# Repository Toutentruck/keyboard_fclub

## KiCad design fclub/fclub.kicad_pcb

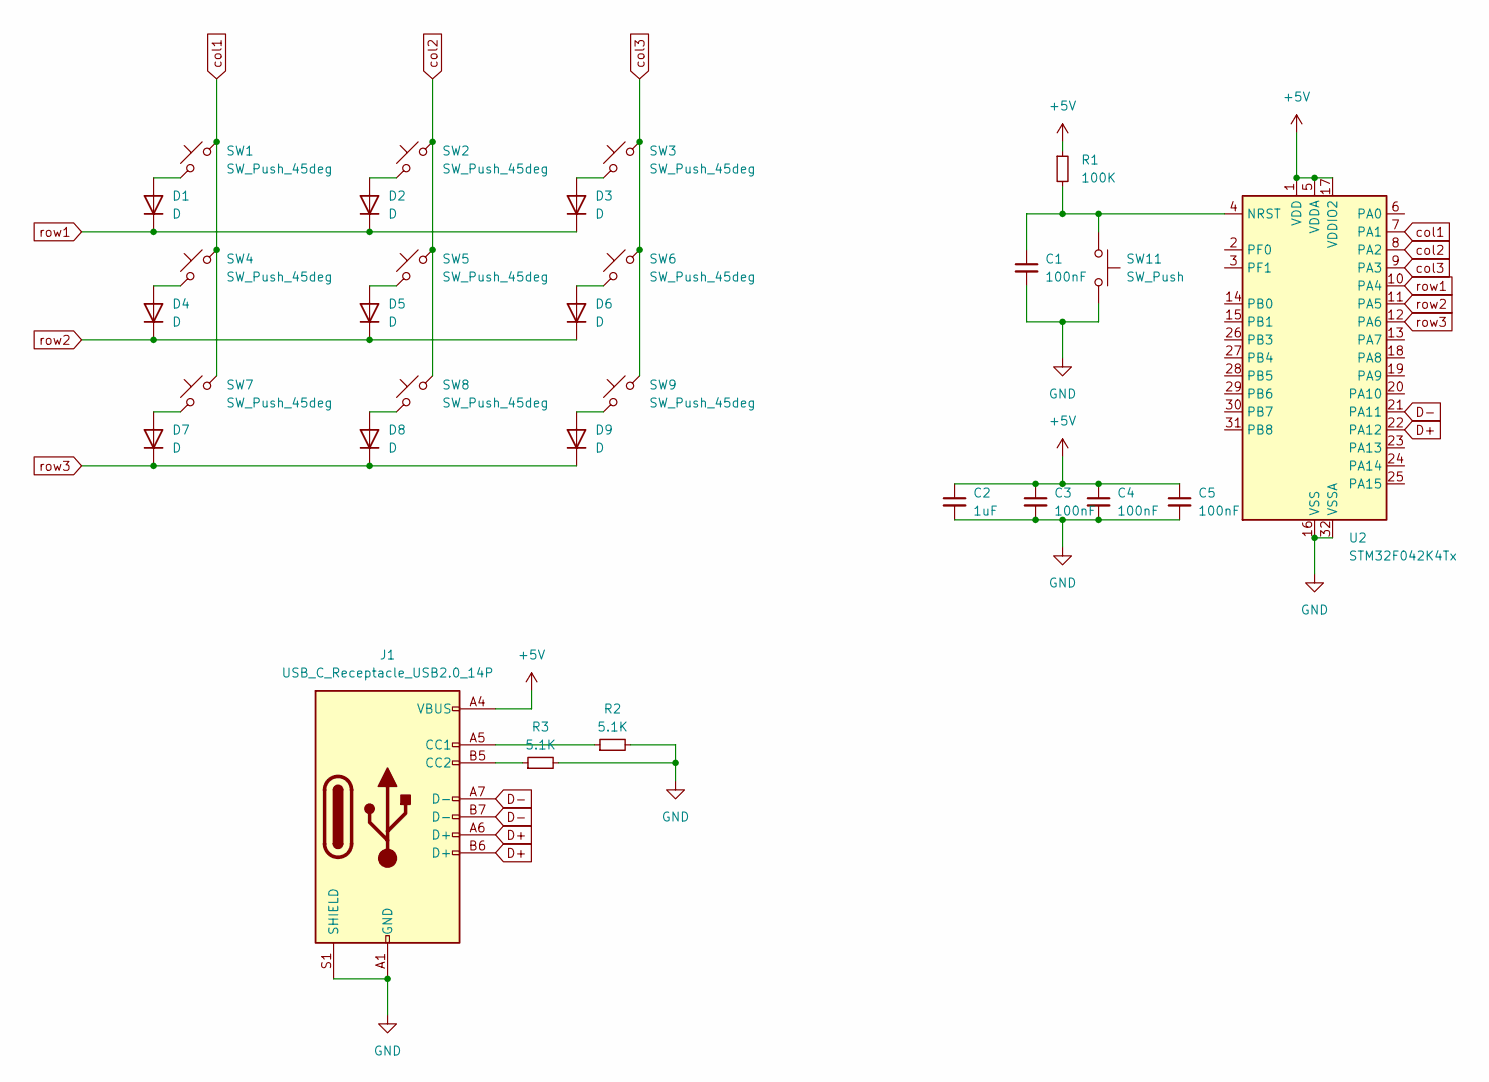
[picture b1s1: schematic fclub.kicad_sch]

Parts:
C1, C3, C4, C5: 100nF; C_0201_0603Metric_Pad0.64x0.40mm_HandSolder
C2: 1uF; C_0201_0603Metric_Pad0.64x0.40mm_HandSolder
D1, D2, D3, D4, D5, D6, D7, D8, D9: D; D_SOD-323_HandSoldering
J1: USB_C_Receptacle_USB2.0_14P; USB_C_Receptacle_GCT_USB4105-xx-A_16P_TopMnt_Horizontal
R1: 100K; R_0201_0603Metric_Pad0.64x0.40mm_HandSolder
R2, R3: 5.1K; R_0201_0603Metric_Pad0.64x0.40mm_HandSolder
SW1, SW2, SW3, SW4, SW5, SW6, SW7, SW8, SW9: SW_Push_45deg; SW_MX_1u
SW11: SW_Push; SKQG-1155865
U2: STM32F042K4Tx; LQFP-32_7x7mm_P0.8mm

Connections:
+5V: C2.1, C3.1, C4.1, C5.1, J1.A4 (VBUS), J1.A9 (VBUS), J1.B4 (VBUS), J1.B9 (VBUS), R1.1, U2.1 (VDD), U2.5 (VDDA), U2.17 (VDDIO2)
D+: J1.A6 (D+), J1.B6 (D+), U2.22 (PA12)
D-: J1.A7 (D-), J1.B7 (D-), U2.21 (PA11)
GND: C1.2, C2.2, C3.2, C4.2, C5.2, J1.A1 (GND), J1.A12 (GND), J1.B1 (GND), J1.B12 (GND), J1.S1 (SHIELD), R2.2, R3.2, SW11.2, U2.16 (VSS), U2.32 (VSSA)
unnamed: D1.2 (A), SW1.1
unnamed: D2.2 (A), SW2.1
unnamed: D3.2 (A), SW3.1
unnamed: D4.2 (A), SW4.1
unnamed: D5.2 (A), SW5.1
unnamed: D6.2 (A), SW6.1
unnamed: D7.2 (A), SW7.1
unnamed: D8.2 (A), SW8.1
unnamed: D9.2 (A), SW9.1
unnamed: J1.A5 (CC1), R2.1
unnamed: J1.B5 (CC2), R3.1
unnamed: C1.1, R1.2, SW11.1, U2.4 (NRST)
col1: SW1.2, SW4.2, SW7.2, U2.7 (PA1)
col2: SW2.2, SW5.2, SW8.2, U2.8 (PA2)
col3: SW3.2, SW6.2, SW9.2, U2.9 (PA3)
row1: D1.1 (K), D2.1 (K), D3.1 (K), U2.10 (PA4)
row2: D4.1 (K), D5.1 (K), D6.1 (K), U2.11 (PA5)
row3: D7.1 (K), D8.1 (K), D9.1 (K), U2.12 (PA6)

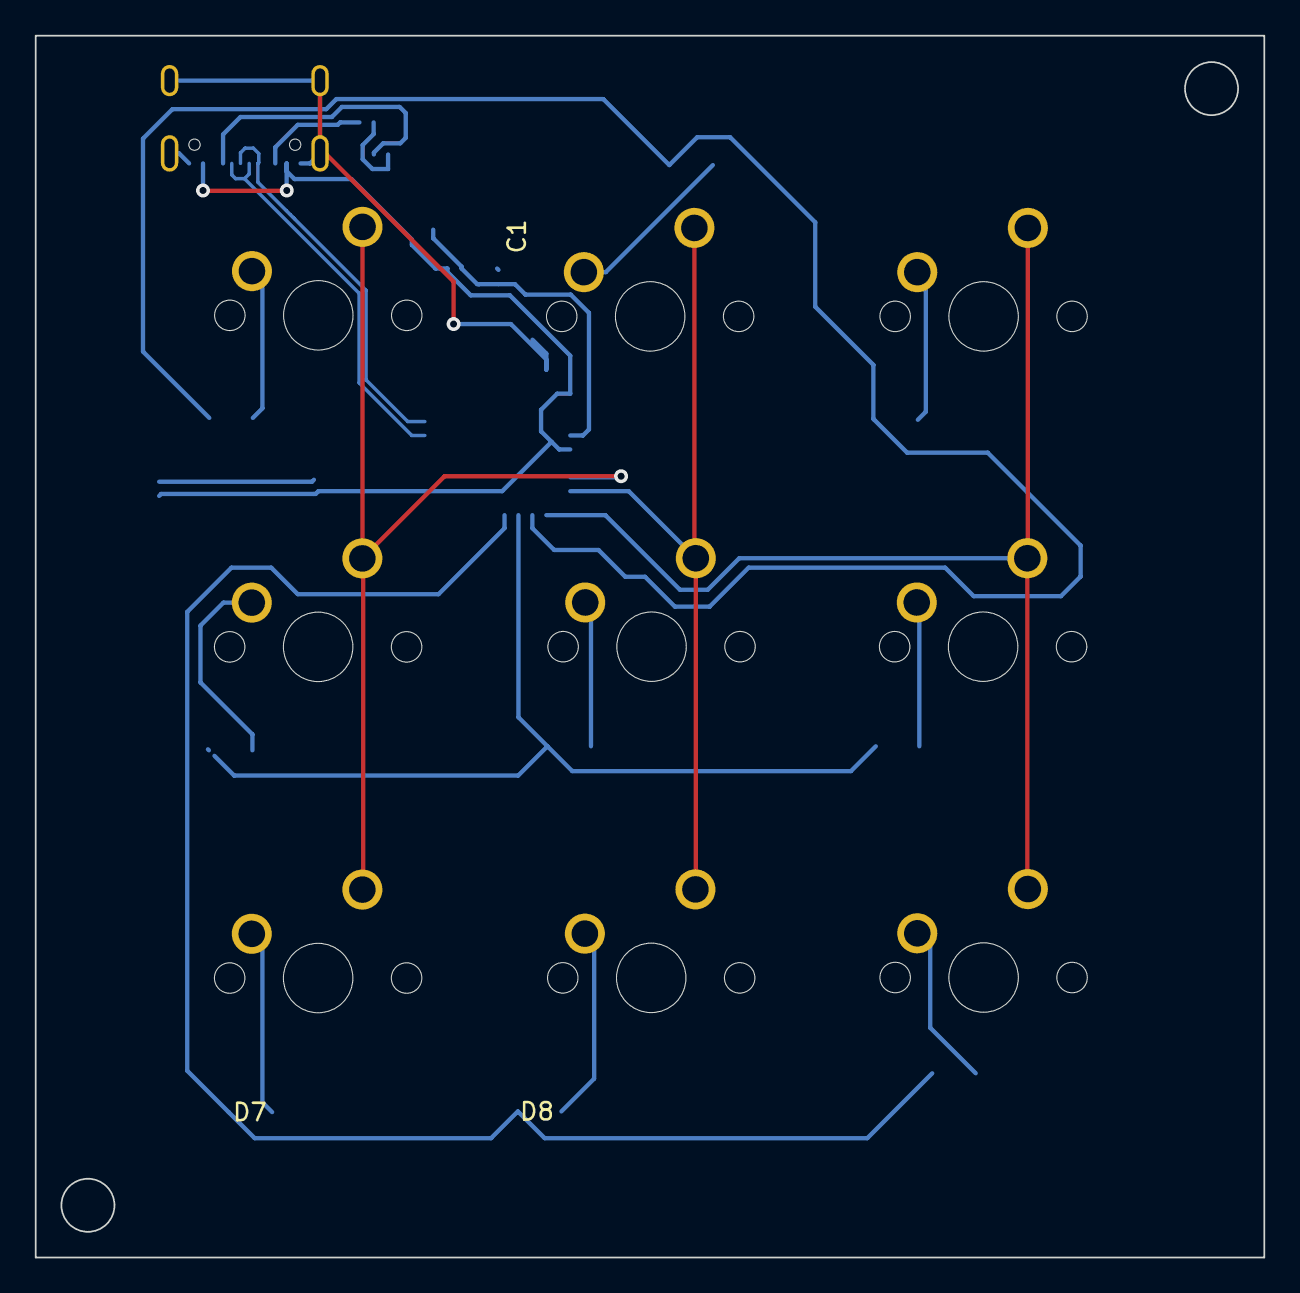
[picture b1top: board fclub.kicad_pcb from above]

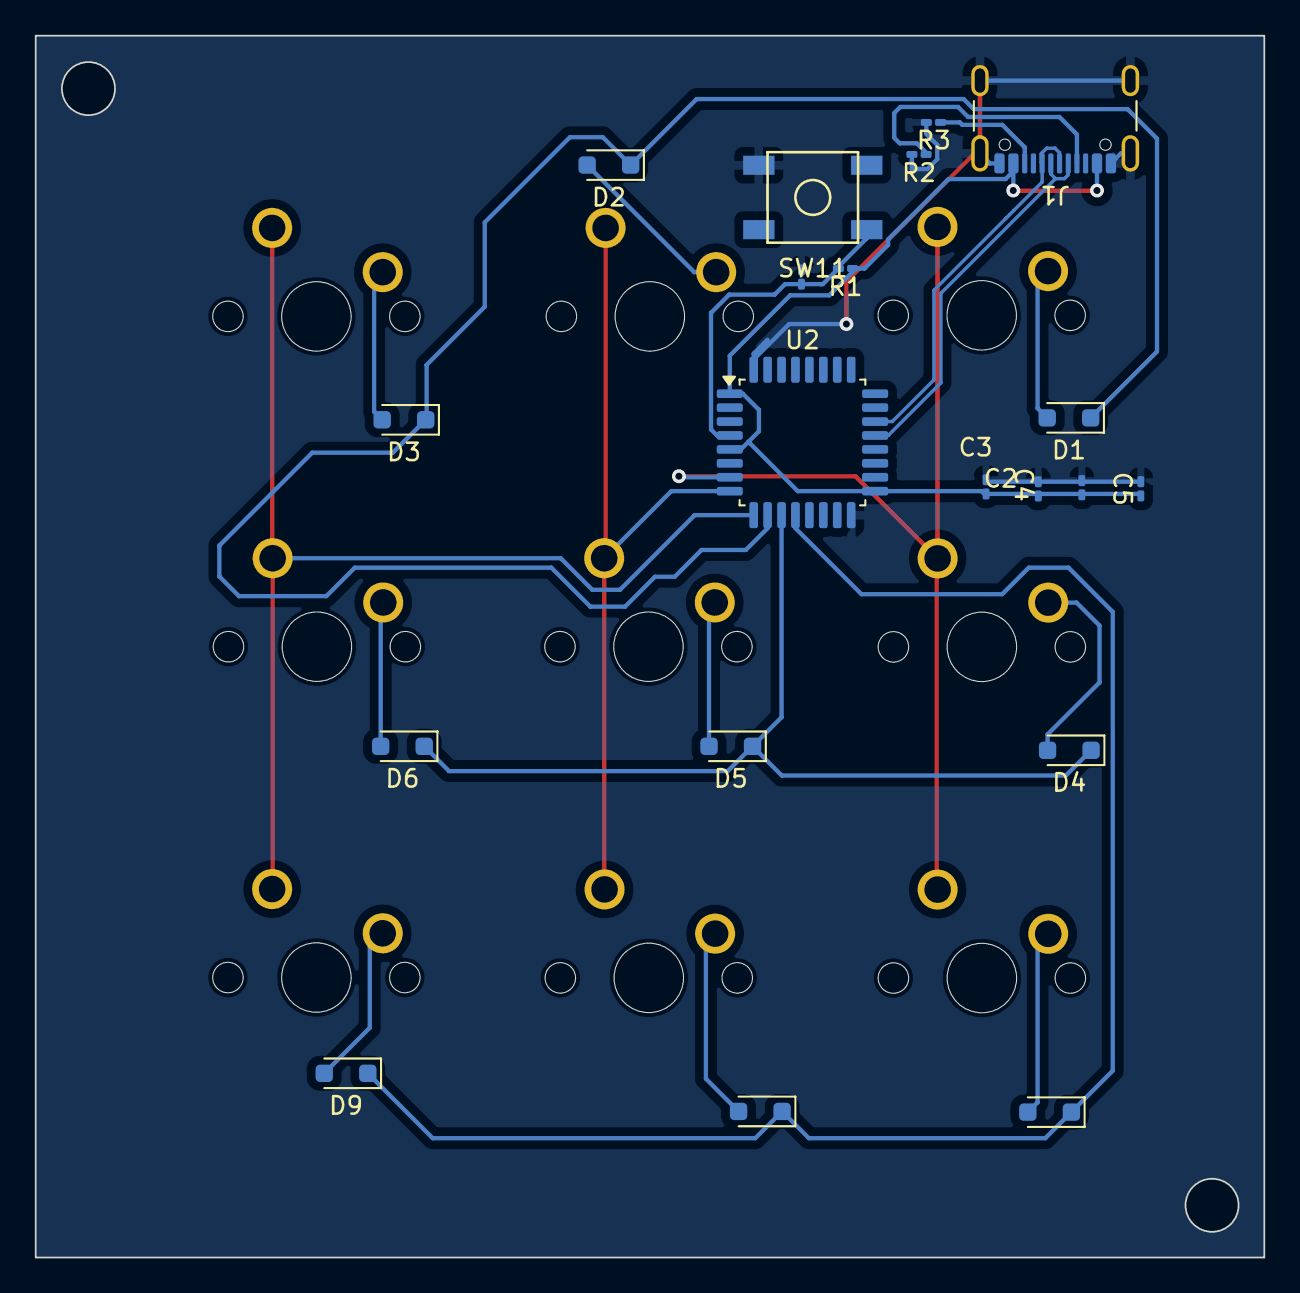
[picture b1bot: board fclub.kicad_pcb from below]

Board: 2 copper layers, 70.6 x 70.2 mm, 29 parts (20 on the bottom side), 22 nets.

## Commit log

2024-08-27 initialize projects
2024-08-27 Add submodules
2024-08-27 add footprint lib
2024-08-27 MCU schematic
2024-08-27 keyboards library
2024-08-28 passage stm
2024-08-28 schematic fini
2024-09-01 pcb fini
